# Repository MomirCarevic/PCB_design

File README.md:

# PCB_design
This will be repository for PCB design projects

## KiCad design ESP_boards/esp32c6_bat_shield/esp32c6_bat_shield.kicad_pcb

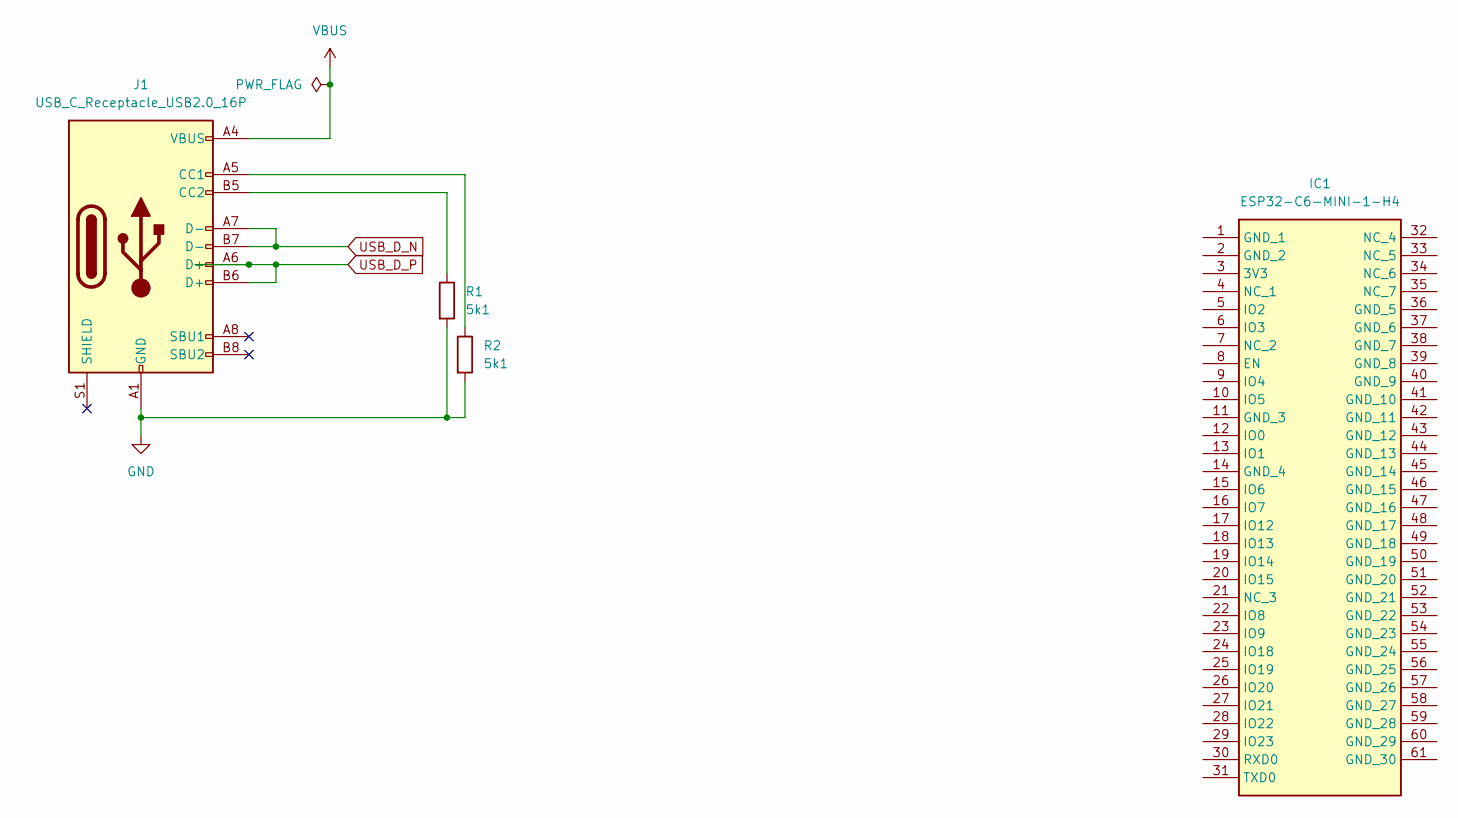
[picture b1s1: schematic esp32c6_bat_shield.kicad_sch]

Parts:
IC1: ESP32-C6-MINI-1-H4; ESP32C6MINI1H4; Mouser Part Number 356-ESP32C6MINI1-H4
J1: USB_C_Receptacle_USB2.0_16P; USB_C_Receptacle_GCT_USB4105-xx-A_16P_TopMnt_Horizontal
R1, R2: 5k1; R_0603_1608Metric

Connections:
GND: J1.A1 (GND), J1.A12 (GND), J1.B1 (GND), J1.B12 (GND), R1.2, R2.2
unnamed: J1.A5 (CC1), R2.1
unnamed: J1.B5 (CC2), R1.1
USB_D_N: J1.A7 (D-), J1.B7 (D-)
USB_D_P: J1.A6 (D+), J1.B6 (D+)
VBUS: J1.A4 (VBUS), J1.A9 (VBUS), J1.B4 (VBUS), J1.B9 (VBUS)

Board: 2 copper layers, 4 parts (0 on the bottom side), 6 nets, no tracks yet.

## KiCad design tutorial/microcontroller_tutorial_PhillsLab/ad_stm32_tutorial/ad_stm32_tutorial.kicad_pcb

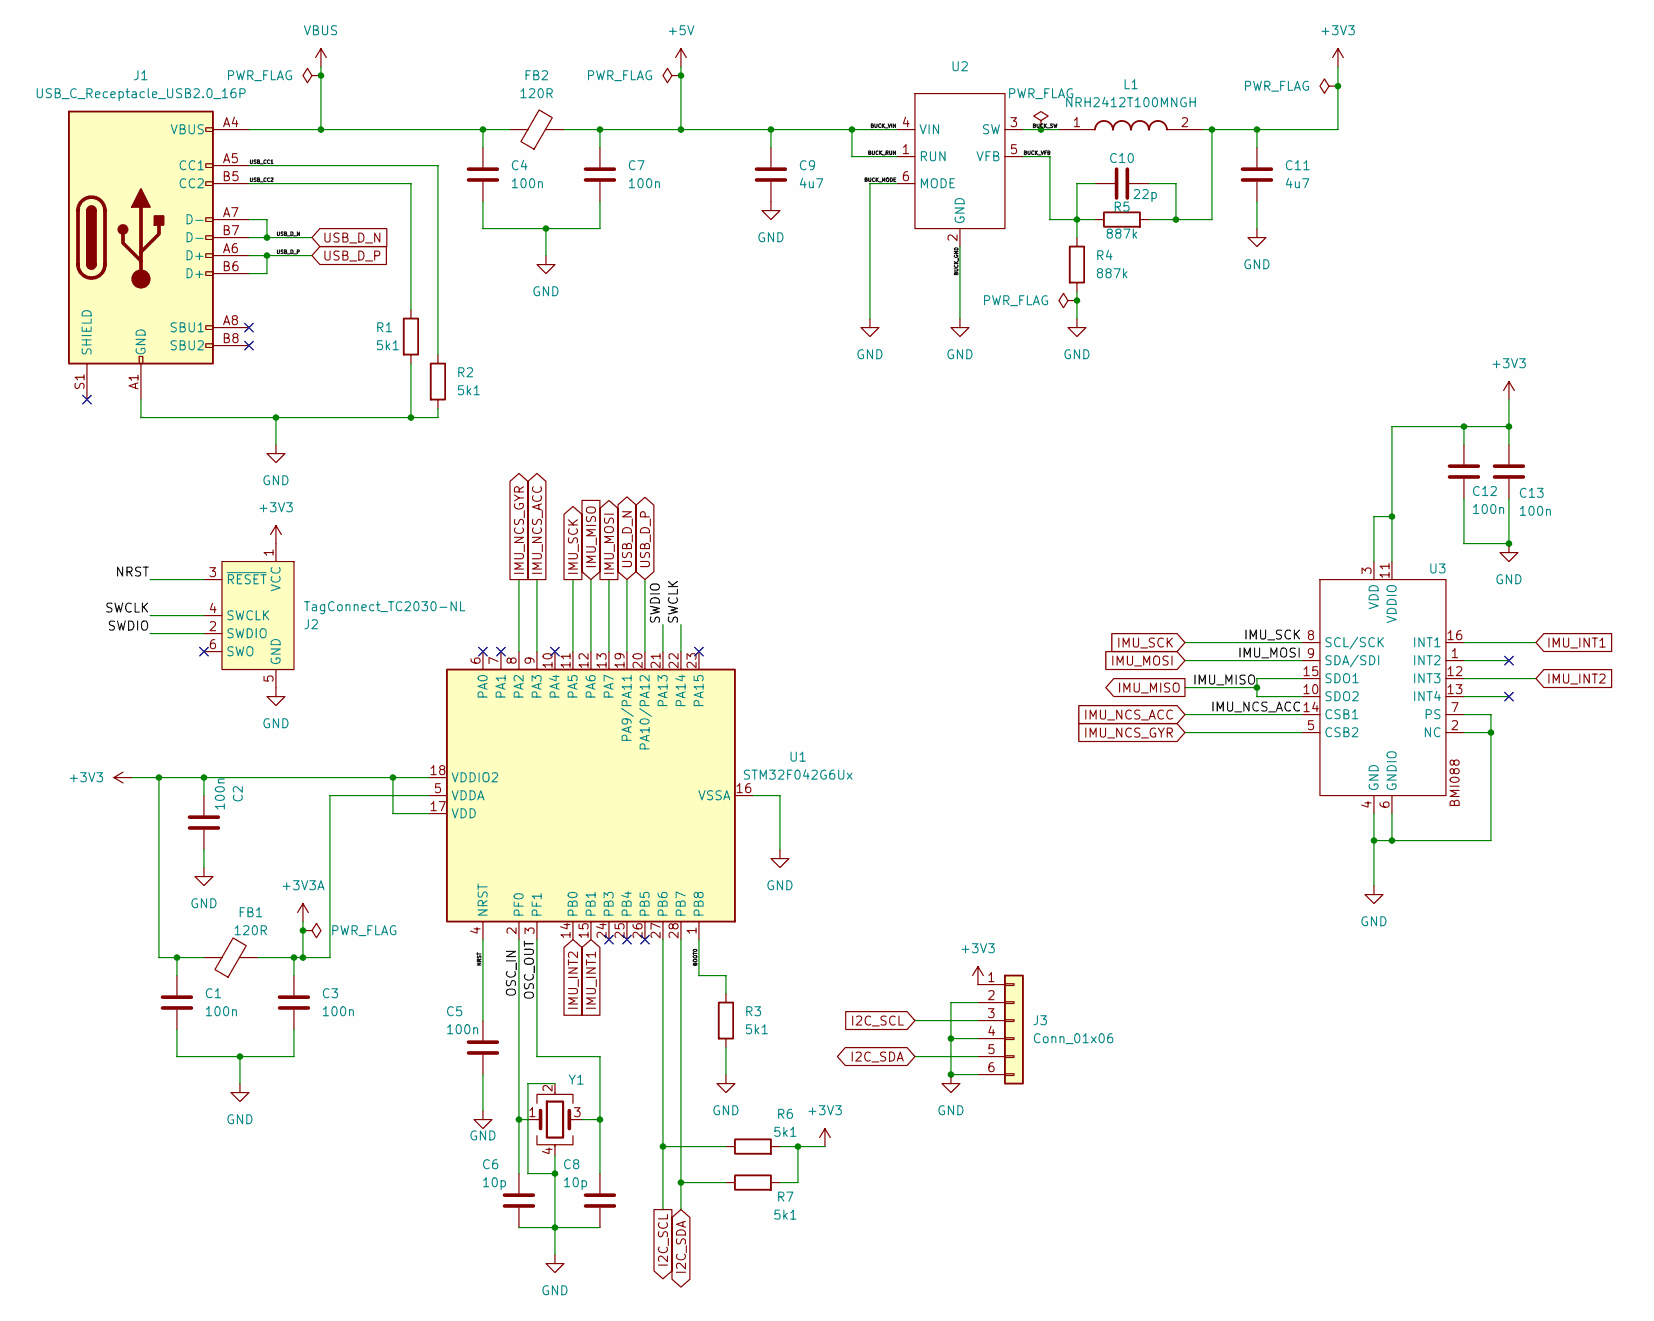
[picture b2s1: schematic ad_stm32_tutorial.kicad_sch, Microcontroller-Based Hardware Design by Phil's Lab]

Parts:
C1, C2, C3, C4, C5, C7, C12, C13: 100n; C_0603_1608Metric
C6, C8: 10p; C_0603_1608Metric
C9, C11: 4u7; C_0805_2012Metric
C10: 22p; C_0603_1608Metric
FB1, FB2: 120R; L_0603_1608Metric
J1: USB_C_Receptacle_USB2.0_16P; USB_C_Receptacle_GCT_USB4105-xx-A_16P_TopMnt_Horizontal
J2: TagConnect_TC2030-NL; Tag-Connect_TC2030-IDC-NL_2x03_P1.27mm_Vertical
J3: Conn_01x06; JST_GH_SM06B-GHS-TB_1x06-1MP_P1.25mm_Horizontal
L1: NRH2412T100MNGH; L_Taiyo-Yuden_NR-24xx; Mouser Part Number 963-NRH2412T100MNGH
R1, R2, R3, R6, R7: 5k1; R_0603_1608Metric
R4, R5: 887k; R_0603_1608Metric
U1: STM32F042G6Ux; QFN-28_4x4mm_P0.5mm
U2: SOT-23-6
U3: LGA-16_4.5x3mm_P0.5mm
Y1: Crystal_GND24; Crystal_SMD_TXC_7M-4Pin_3.2x2.5mm

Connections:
+3V3: C1.1, C2.2, C10.2, C11.1, C12.1, C13.1, FB1.1, J2.1 (VCC), J3.1, L1.2, R5.2, R6.2, R7.2, U1.17 (VDD), U1.18 (VDDIO2), U3.3 (VDD), U3.11 (VDDIO)
+3V3A: C3.1, FB1.2, U1.5 (VDDA)
+5V: C7.1, C9.1, FB2.2, U2.1 (RUN), U2.4 (VIN)
/BOOT0: R3.1, U1.1 (PB8)
/BUCK_SW: L1.1, U2.3 (SW)
/BUCK_VFB: C10.1, R4.1, R5.1, U2.5 (VFB)
/NRST: C5.1, J2.3 (~RESET), U1.4 (NRST)
/OSC_IN: C6.1, U1.2 (PF0), Y1.1
/OSC_OUT: C8.1, U1.3 (PF1), Y1.3
/SWCLK: J2.4 (SWCLK), U1.22 (PA14)
/SWDIO: J2.2 (SWDIO), U1.21 (PA13)
/USB_CC1: J1.A5 (CC1), R2.1
/USB_CC2: J1.B5 (CC2), R1.1
GND: C1.2, C2.1, C3.2, C4.2, C5.2, C6.2, C7.2, C8.2, C9.2, C11.2, C12.2, C13.2, J1.A1 (GND), J1.A12 (GND), J1.B1 (GND), J1.B12 (GND), J2.5 (GND), J3.2, J3.4, J3.6, R1.2, R2.2, R3.2, R4.2, U1.16 (VSSA), U2.2 (GND), U2.6 (MODE), U3.2 (NC), U3.4 (GND), U3.6 (GNDIO), U3.7 (PS), Y1.2, Y1.4
I2C_SCL: J3.3, R6.1, U1.27 (PB6)
I2C_SDA: J3.5, R7.1, U1.28 (PB7)
IMU_INT1: U1.15 (PB1), U3.16 (INT1)
IMU_INT2: U1.14 (PB0), U3.12 (INT3)
IMU_MISO: U1.12 (PA6), U3.10 (SDO2), U3.15 (SDO1)
IMU_MOSI: U1.13 (PA7), U3.9 (SDA/SDI)
IMU_NCS_ACC: U1.9 (PA3), U3.14 (CSB1)
IMU_NCS_GYR: U1.8 (PA2), U3.5 (CSB2)
IMU_SCK: U1.11 (PA5), U3.8 (SCL/SCK)
USB_D_N: J1.A7 (D-), J1.B7 (D-), U1.19 (PA9/PA11)
USB_D_P: J1.A6 (D+), J1.B6 (D+), U1.20 (PA10/PA12)
VBUS: C4.1, FB2.1, J1.A4 (VBUS), J1.A9 (VBUS), J1.B4 (VBUS), J1.B9 (VBUS)

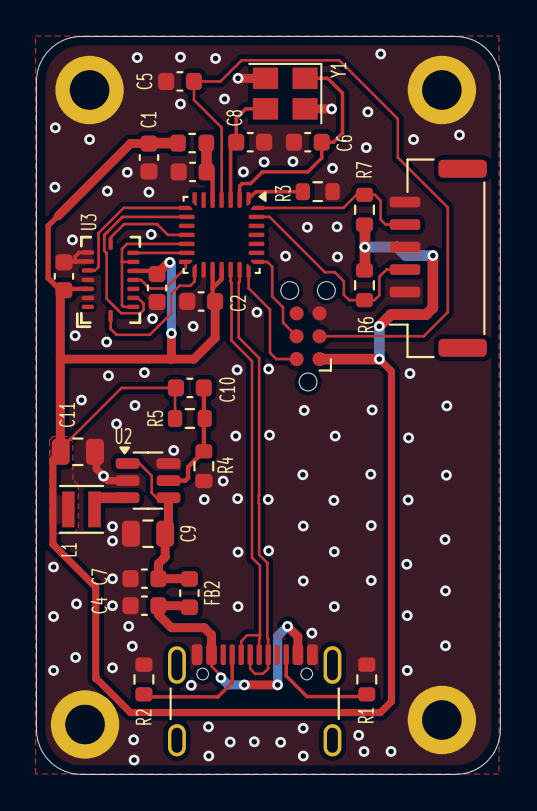
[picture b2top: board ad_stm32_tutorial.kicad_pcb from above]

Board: 2 copper layers, 25.8 x 41.0 mm, 30 parts (0 on the bottom side), 26 nets.

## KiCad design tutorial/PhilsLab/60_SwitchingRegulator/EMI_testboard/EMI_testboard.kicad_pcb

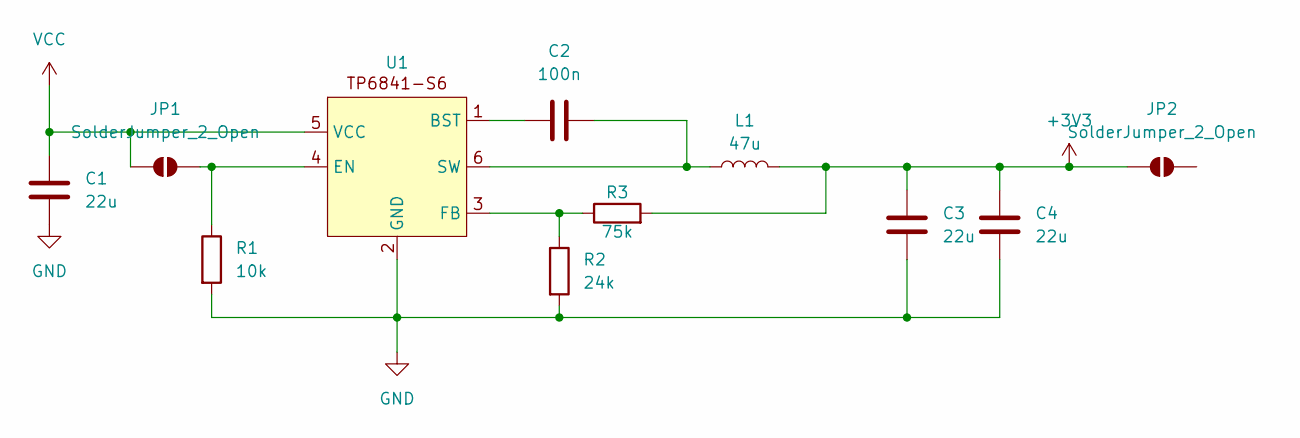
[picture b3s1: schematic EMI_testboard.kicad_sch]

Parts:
C1, C3, C4: 22u; C_1210_3225Metric
C2: 100n; C_0603_1608Metric
JP1, JP2: SolderJumper_2_Open; SolderJumper-2_P1.3mm_Open_TrianglePad1.0x1.5mm
L1: 47u; L_Neosid_SM-PIC0512H
R1: 10k; C_0603_1608Metric
R2: 24k; C_0603_1608Metric
R3: 75k; C_0603_1608Metric
U1: SOT-23-6

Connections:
+3V3: C3.1, C4.1, JP2.1 (A), L1.2, R3.2
GND: C1.2, C3.2, C4.2, R1.2, R2.2, U1.2 (GND)
unnamed: JP1.2 (B), R1.1, U1.4 (EN)
unnamed: C2.2, U1.1 (BST)
unnamed: R2.1, R3.1, U1.3 (FB)
unnamed: C2.1, L1.1, U1.6 (SW)
VCC: C1.1, JP1.1 (A), U1.5 (VCC)

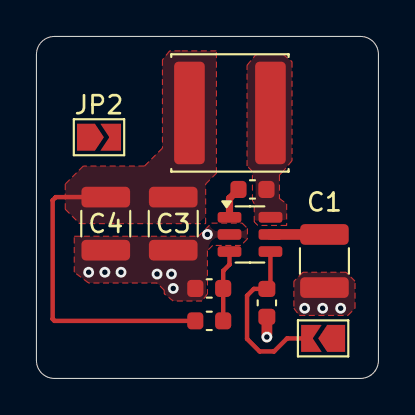
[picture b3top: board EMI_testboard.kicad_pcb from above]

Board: 2 copper layers, 19.0 x 19.0 mm, 11 parts (0 on the bottom side), 7 nets.

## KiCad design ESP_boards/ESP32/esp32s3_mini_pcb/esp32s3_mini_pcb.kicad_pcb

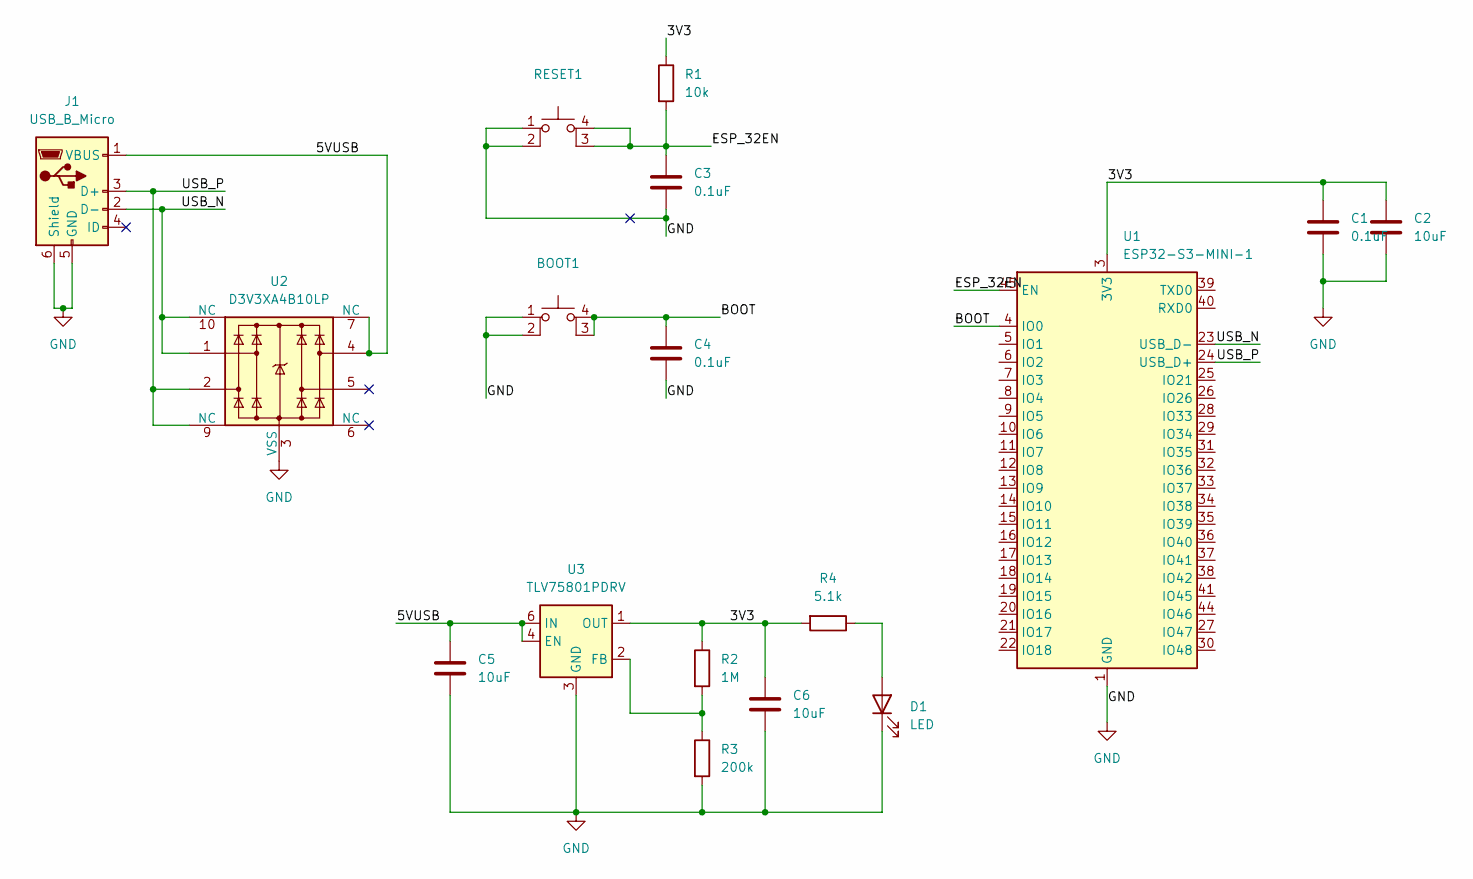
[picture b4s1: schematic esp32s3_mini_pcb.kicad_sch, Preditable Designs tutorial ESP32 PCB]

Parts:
BOOT1: SW_MEC_5E; SW_SPST_PTS810
C1, C3, C4: 0.1uF; C_0603_1608Metric
C2, C5, C6: 10uF; C_0603_1608Metric
D1: LED; LED_0603_1608Metric
J1: USB_B_Micro; USB_Micro-B_GCT_USB3076-30-A
R1: 10k; R_0603_1608Metric
R2: 1M; R_0603_1608Metric
R3: 200k; R_0603_1608Metric
R4: 5.1k; R_0603_1608Metric
RESET1: SW_MEC_5E; SW_SPST_PTS810
U1: ESP32-S3-MINI-1; ESP32-S2-MINI-1
U2: D3V3XA4B10LP; Diodes_UDFN-10_1.0x2.5mm_P0.5mm
U3: TLV75801PDRV; WSON-6-1EP_2x2mm_P0.65mm_EP1x1.6mm

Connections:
/3V3: C1.1, C2.1, C6.1, R1.1, R2.1, R4.2, U1.3 (3V3), U3.1 (OUT)
/5VUSB: C5.1, J1.1 (VBUS), U2.4, U2.7 (NC), U3.4 (EN), U3.6 (IN)
/BOOT: BOOT1.3 (K), BOOT1.4 (A), C4.1, U1.4 (IO0)
/ESP_32EN: C3.1, R1.2, RESET1.3 (K), RESET1.4 (A), U1.45 (EN)
/USB_N: J1.2 (D-), U1.23 (USB_D-), U2.1, U2.10 (NC)
/USB_P: J1.3 (D+), U1.24 (USB_D+), U2.2, U2.9 (NC)
GND: BOOT1.1, BOOT1.2, C1.2, C2.2, C3.2, C4.2, C5.2, C6.2, D1.1 (K), J1.5 (GND), J1.6 (Shield), R3.2, RESET1.1, RESET1.2, U1.1 (GND), U1.2 (GND), U1.42 (GND), U1.43 (GND), U1.46 (GND), U1.47 (GND), U1.48 (GND), U1.49 (GND), U1.50 (GND), U1.51 (GND), U1.52 (GND), U1.53 (GND), U1.54 (GND), U1.55 (GND), U1.56 (GND), U1.57 (GND), U1.58 (GND), U1.59 (GND), U1.60 (GND), U1.61 (GND), U1.62 (GND), U1.63 (GND), U1.64 (GND), U1.65 (GND), U2.3 (VSS), U2.8 (VSS), U3.3 (GND), U3.7 (GND)
unnamed: D1.2 (A), R4.1
unnamed: R2.2, R3.1, U3.2 (FB)

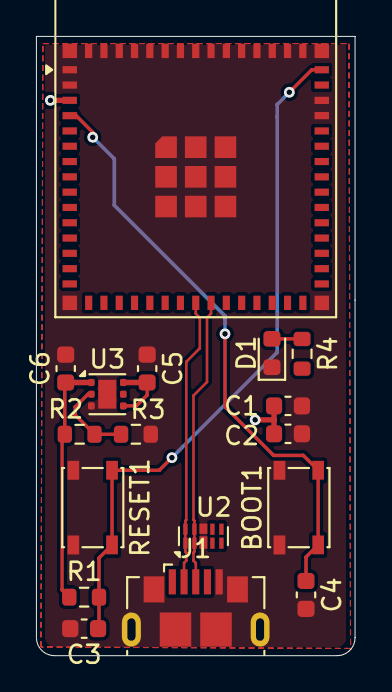
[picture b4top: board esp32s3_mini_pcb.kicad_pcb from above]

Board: 4 copper layers, 17.7 x 34.4 mm, 17 parts (0 on the bottom side), 9 nets.

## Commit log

2025-02-27 ESP :: Started Predicable Designs tutorial 'How to design an ESP32 PCB with KiCad'
2025-02-27 ESP :: Work on the schematic
2025-02-27 ESP :: Finished Schematic
2025-02-27 ESP :: Laptop can't keep up, we will try at home
2025-02-28 Working on PCB
2025-02-28 Finished the board
2025-03-02 TUTORIAL :: Started Phil's lab tutorial on Altium Academy which is composed out of 11 parts.
2025-03-04 BUCK CONVERTER :: #60 video finished schematic
2025-03-04 BUCK CONVERTER :: Changed capacitors
2025-03-04 Finished Buck converter from video #60
2025-03-04 VIDEO #3 :: finished schematic
2025-03-04 VIDEO #3 :: Added USB-C connector
2025-03-04 Started BuckConverter board with LM2596
2025-03-05 Finished Video 4 of Phil's Lab Microcontroller-Based Hardware Design tutorial
2025-03-05 Phil's lab Microcontroller tutorial - Started adding sensor
2025-03-05 Adding BMI088 to project
2025-03-06 Finished schematic
2025-03-06 Updated schematic
2025-03-06 Changed few footprints for stm32 project
2025-03-06 Started PCB Layout of power section
2025-03-06 Started adding MCU (STM32F4) and it's components
2025-03-06 Finished placement of all the components
2025-03-06 Added mounting hole to my PCB design, it's enough for tonight. Stopped on video 9
2025-03-07 Finished power section
2025-03-07 Added all the traces and connecting Via's. Check out ViaStitching tool on github
2025-03-07 Checking DRC
2025-03-07 Finished PCB design, just need to add silkscreen
2025-03-07 Finished!
2025-03-07 Added all 3d models
2025-03-10 Started creating Battery shield for ESP32-c6 dev board
2025-03-12 Added schematic, footprint and 3d model for ESP32-C6-MINI to parts folder
2025-03-12 Added USB-C connector
2025-03-12 Added esp32c6-mini to library
2025-03-14 Schematic of the LDO is finished and gerber files are exported
2025-03-14 Updated .PrjPcb file
2025-03-14 Started new project
2025-03-18 Playing with libraries for IMU BMI270 from bosch
2025-03-21 Started new breakout board for BMI270
2025-03-21 Added schematic and PCB documents
2025-03-21 Updated BMI270_brekaout.PrjPcb file
2025-03-21 Updated BMI270_breakout.PrjPcb file
2025-03-21 Finished schematic, need to add footprints for capacitors, BMI270 and 12 pin connector
2025-03-24 Added footprint for BMI270
2025-03-24 Finished BMI270 breakout board
2025-03-24 BMI270 breakout board - Updated silk screen
2025-03-24 Deleted ESP board projects, starting over
2025-03-24 ESP32-C6-MINI :: Started new PCB design for board that is powerd via battery
2025-03-24 Added esp32c6-mini to my library, need to condesate 23 GND pins to one pin
2025-03-26 ESP32 :: Added esp32c6-mini footprint to the moma_altium library
2025-03-26 Before restructuring the project
2025-03-26 renaming Sheet1
2025-03-26 Renamed schematic1 to 0_ESP_batt_shield-Overview and added 1_ESP_batt_shield-Power schematic
2025-03-26 Added MCU and sensors schematic doc
2025-03-26 BATTERY SHIELD :: Started power path design
2025-03-26 Added 0603 capacitor and resistor to moma_altium library
2025-03-26 Added TPS63000 to and wired it up. Check if the inductor is the proper size!
2025-03-26 Added usb C library to moma_altium library
2025-03-26 Need to resolve problems with not finding custom made footprints
2025-03-27 Updated folder name
2025-03-27 Added Ferrite Bead to the schematic library
2025-03-27 Started MCU and Sensor schematic, power is finished. Check if you need to add pi lowpass filter (Ferrite bead) between USB VBUS and input of buck-boost converter
2025-03-27 Changed ESP32-c6-mini, changed schematic symbol and started working on MCU schematic
2025-03-27 Changes to be committed: new file: Altium libraries/moma_altium_library/3d_models/tactile_switches/PTS645SH50SMTR92LFS.stp new file: Altium libraries/moma_altium_library/3d_models/tactile_switches/PT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
2025-03-27 modified: Altium libraries/moma_altium_library/moma_altium_library.SchLib
2025-03-27 Added symbol and footprint(SOD-523) for bidirectional TWS diode LESD5D5.0CT1G. Files that were modified: modified: Altium libraries/moma_altium_library/moma_altium_PCBlibrary.PcbLib modified: Altium 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
2025-03-27 modified: Altium libraries/moma_altium_library/moma_altium_library.SchLib modified: ESP_boards/esp32c6-mini/Battery_shield/1_ESP_batt_shield-Power.SchDoc
2025-03-27 Commited changes: modified: Altium libraries/moma_altium_library/moma_altium_PCBlibrary.PcbLib modified: Altium libraries/moma_altium_library/moma_altium_library.SchLib modified: ESP_boards/esp32c6-m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
2025-03-28 Changes to be committed: deleted: Altium libraries/moma_altium_library.IntLib modified: Altium libraries/moma_altium_library/moma_altium_PCBlibrary.PcbLib deleted: Altium libraries/moma_altium_librar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
    Untracked files:
    Altium libraries/moma_altium_library.IntLib
2025-04-01 Added BMI270 to the project
2025-04-01 Changes to be committed: modified: ESP_boards/esp32c6-mini/Battery_shield/1_ESP_batt_shield-Power.SchDoc modified: ESP_boards/esp32c6-mini/Battery_shield/2_ESP_batt_shield-MCU_and_sensors.SchDoc
2025-04-01 Finished schematic of this board.
    Changes to be committed:
    modified: ESP_boards/esp32c6-mini/Battery_shield/1_ESP_batt_shield-Power.SchDoc
    modified: ESP_boards/esp32c6-mini/Battery_shield/2_ESP_batt_shield-MCU_and_sensors.SchDoc
    deleted: ESP_boards/esp32c6-mini/Battery_shield/PCB1.PcbDoc
2025-04-01 Added overview sheet.
    Changes to be committed:
    modified: ESP_boards/esp32c6-mini/Battery_shield/0_ESP_batt_shield-Overview.SchDoc
    modified: ESP_boards/esp32c6-mini/Battery_shield/2_ESP_batt_shield-MCU_and_sensors.SchDoc
    modified: ESP_boards/esp32c6-mini/Battery_shield/battery_shield.PrjPcb
2025-04-01 Added PCB doc and started working on PCB design.
    Changes to be committed:
    modified: ESP_boards/esp32c6-mini/Battery_shield/1_ESP_batt_shield-Power.SchDoc
    new file: ESP_boards/esp32c6-mini/Battery_shield/PCB1.PcbDoc
    modified: ESP_boards/esp32c6-mini/Battery_shield/battery_shield.PrjPcb
2025-04-02 Added design rules
2025-04-02 Finished initial layout, routing is next
    Changes to be committed:
    modified: ESP_boards/esp32c6-mini/Battery_shield/1_ESP_batt_shield-Power.SchDoc
    modified: ESP_boards/esp32c6-mini/Battery_shield/PCB1.PcbDoc
2025-04-02 Changes to be committed: modified: ESP_boards/esp32c6-mini/Battery_shield/1_ESP_batt_shield-Power.SchDoc modified: ESP_boards/esp32c6-mini/Battery_shield/PCB1.PcbDoc
2025-04-02 Changes to be committed: modified: ESP_boards/esp32c6-mini/Battery_shield/PCB1.PcbDoc
2025-04-02 Changed routing in power part of PCB. Deleted differential pair routing because of wrong placement of IMU and ESP mcu.
    Changes to be committed:
    modified: ESP_boards/esp32c6-mini/Battery_shield/PCB1.PcbDoc
2025-04-03 Changes to be committed: modified: ESP_boards/esp32c6-mini/Battery_shield/2_ESP_batt_shield-MCU_and_sensors.SchDoc modified: ESP_boards/esp32c6-mini/Battery_shield/PCB1.PcbDoc
2025-04-03 Finished PCB, I dont like positioning. This PCB design needs redo
    Changes to be committed:
    modified: ESP_boards/esp32c6-mini/Battery_shield/2_ESP_batt_shield-MCU_and_sensors.SchDoc
    modified: ESP_boards/esp32c6-mini/Battery_shield/PCB1.PcbDoc
2025-04-03 Added ground pours.
    Changes to be committed:
    modified: ESP_boards/esp32c6-mini/Battery_shield/PCB1.PcbDoc
